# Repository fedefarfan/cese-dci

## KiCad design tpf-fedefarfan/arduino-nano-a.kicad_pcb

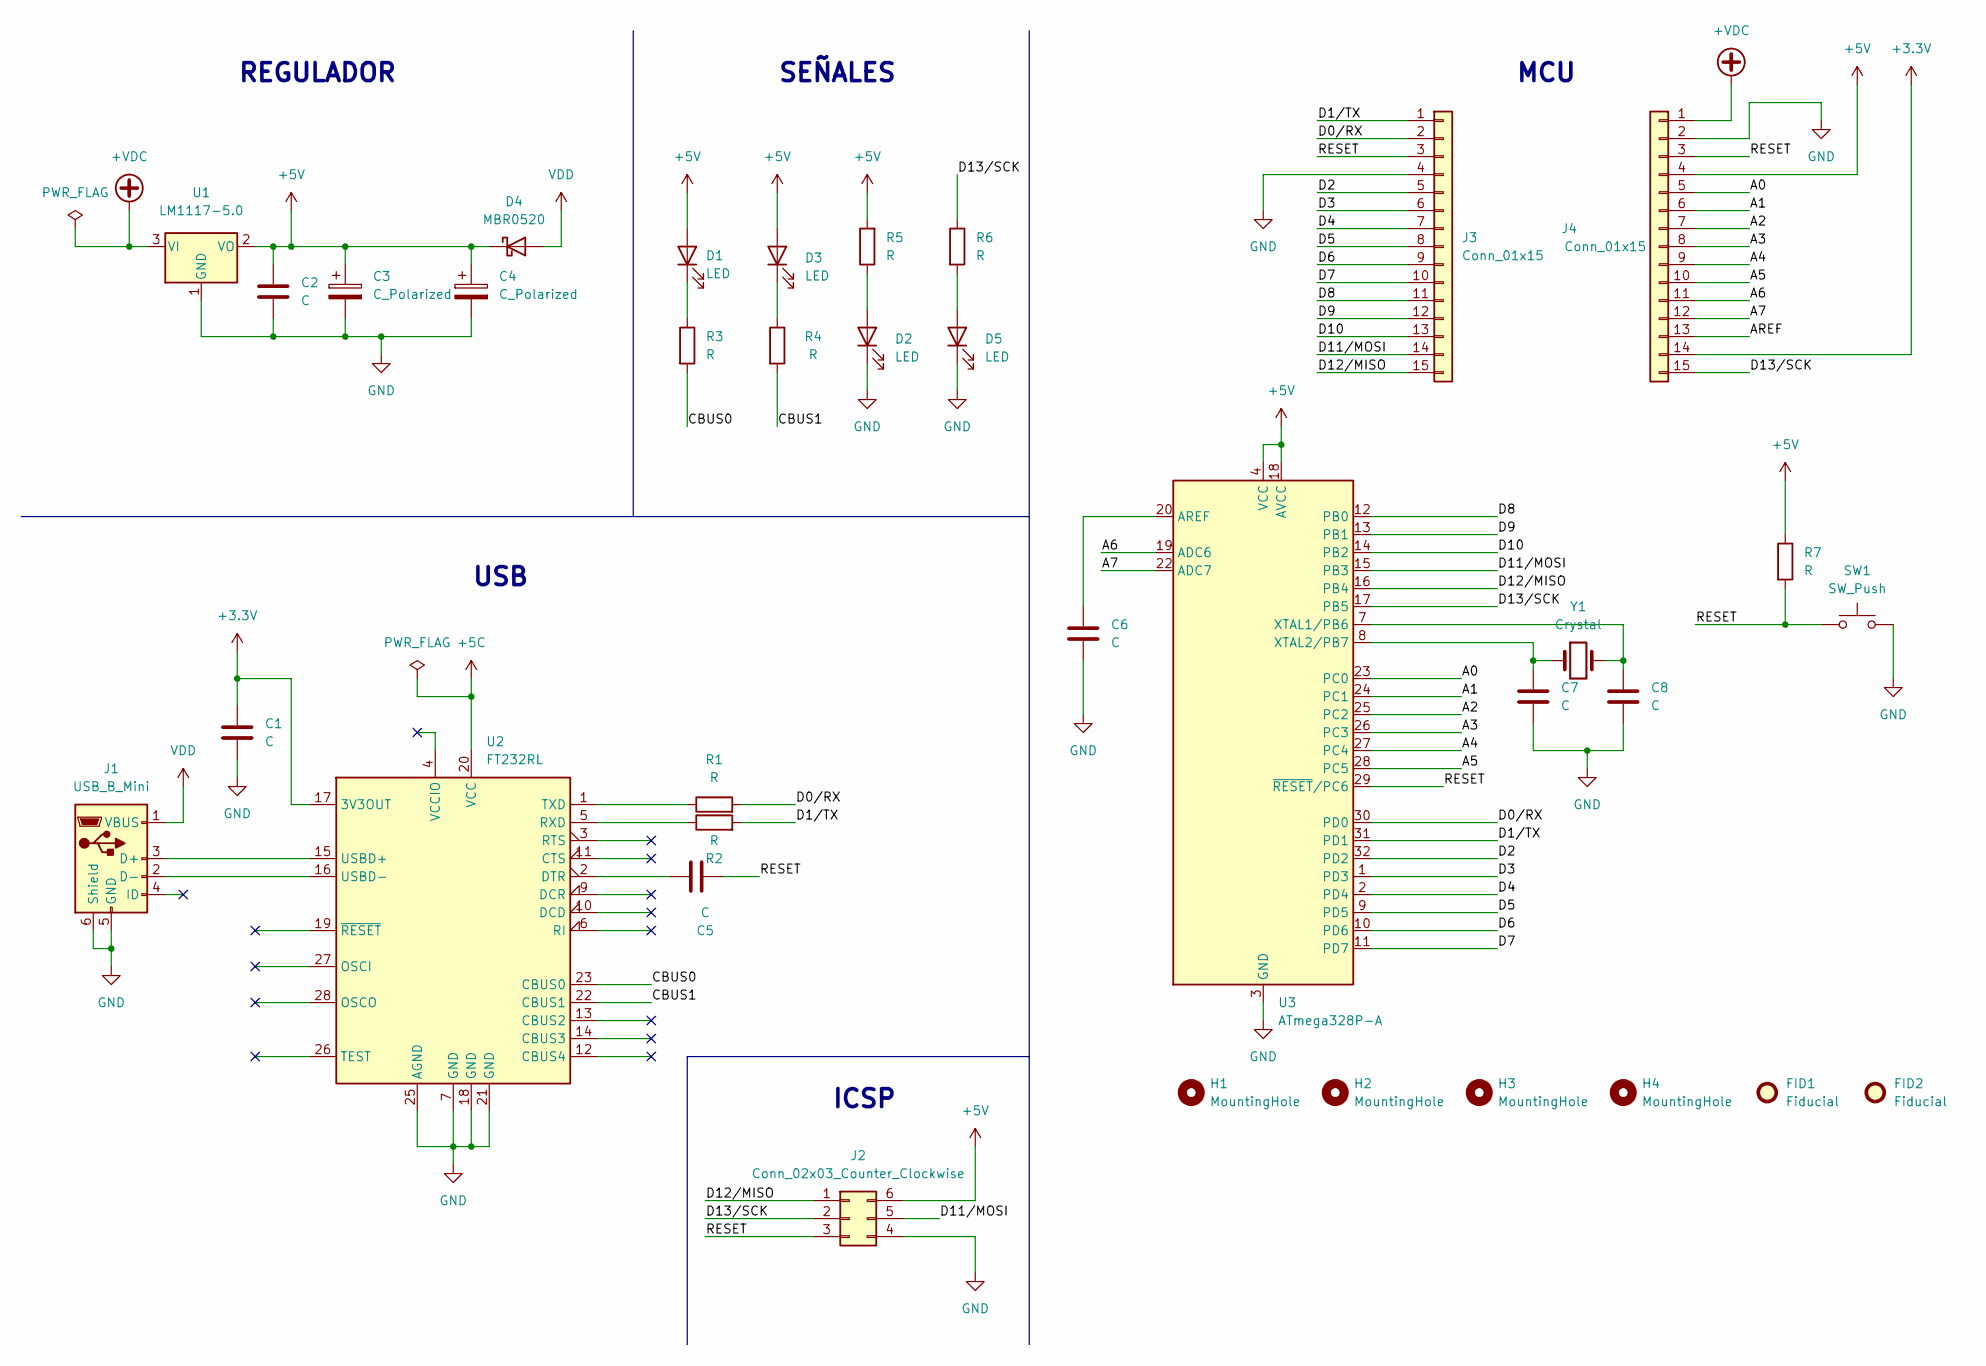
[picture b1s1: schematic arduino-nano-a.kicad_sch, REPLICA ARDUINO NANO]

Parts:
C1: C
C2, C5, C6, C7, C8: C; CP_EIA-3216-18_Kemet-A_Pad1.58x1.35mm_HandSolder
C3, C4: C_Polarized; CP_Elec_3x5.3
D1, D2, D3, D5: LED; LED_0805_2012Metric_Pad1.15x1.40mm_HandSolder
D4: MBR0520; D_SOD-123
FID1, FID2: Fiducial; Fiducial_1mm_Mask2mm
H1, H2, H3, H4: MountingHole; MountingHole_2.2mm_M2_ISO7380
J1: USB_B_Mini; USB_Mini-B_Lumberg_2486_01_Horizontal
J2: Conn_02x03_Counter_Clockwise; PinHeader_2x03_P2.54mm_Vertical
J3, J4: Conn_01x15; PinHeader_1x15_P2.54mm_Vertical
R1, R2, R3, R4, R5, R6, R7: R; R_0201_0603Metric
SW1: SW_Push; SW_SPST_FSMSM
U1: LM1117-5.0; SOT-223-3_TabPin2
U2: FT232RL; SSOP-28_5.3x10.2mm_P0.65mm
U3: ATmega328P-A; TQFP-32_7x7mm_P0.8mm
Y1: Crystal; Crystal_HC49-U_Vertical

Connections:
+3.3V: C1.1, J4.14, U2.17 (3V3OUT)
+5C: U2.20 (VCC)
+5V: C2.1, C3.1, C4.1, D1.2 (A), D3.2 (A), D4.1 (K), J2.6, J4.4, R5.2, R7.1, U1.2 (VO), U3.4 (VCC), U3.6 (VCC), U3.18 (AVCC)
+VDC: J4.1, U1.3 (VI)
/A0: J4.5, U3.23 (PC0)
/A1: J4.6, U3.24 (PC1)
/A2: J4.7, U3.25 (PC2)
/A3: J4.8, U3.26 (PC3)
/A4: J4.9, U3.27 (PC4)
/A5: J4.10, U3.28 (PC5)
/A6: J4.11, U3.19 (ADC6)
/A7: J4.12, U3.22 (ADC7)
/AREF: J4.13
/CBUS0: R3.2, U2.23 (CBUS0)
/CBUS1: R4.2, U2.22 (CBUS1)
/D0/RX: J3.2, R1.2, U3.30 (PD0)
/D1/TX: J3.1, R2.2, U3.31 (PD1)
/D2: J3.5, U3.32 (PD2)
/D3: J3.6, U3.1 (PD3)
/D4: J3.7, U3.2 (PD4)
/D5: J3.8, U3.9 (PD5)
/D6: J3.9, U3.10 (PD6)
/D7: J3.10, U3.11 (PD7)
/D8: J3.11, U3.12 (PB0)
/D9: J3.12, U3.13 (PB1)
/D10: J3.13, U3.14 (PB2)
/D11/MOSI: J2.5, J3.14, U3.15 (PB3)
/D12/MISO: J2.1, J3.15, U3.16 (PB4)
/D13/SCK: J2.2, J4.15, R6.1, U3.17 (PB5)
/RESET: C5.2, J2.3, J3.3, J4.2, J4.3, R7.2, SW1.1, U3.29 (~RESET/PC6)
GND: C1.2, C2.2, C3.2, C4.2, C6.2, C7.2, C8.2, D2.1 (K), D5.1 (K), J1.5 (GND), J1.6 (Shield), J2.4, J3.4, J4.2, SW1.2, U1.1 (GND), U2.7 (GND), U2.18 (GND), U2.21 (GND), U2.25 (AGND), U3.3 (GND), U3.5 (GND), U3.21 (GND)
unnamed: C5.1, U2.2 (DTR)
unnamed: C6.1, U3.20 (AREF)
unnamed: C7.1, U3.8 (XTAL2/PB7), Y1.1
unnamed: C8.1, U3.7 (XTAL1/PB6), Y1.2
unnamed: D1.1 (K), R3.1
unnamed: D2.2 (A), R5.1
unnamed: D3.1 (K), R4.1
unnamed: D5.2 (A), R6.2
unnamed: J1.2 (D-), U2.16 (USBD-)
unnamed: J1.3 (D+), U2.15 (USBD+)
unnamed: R1.1, U2.1 (TXD)
unnamed: R2.1, U2.5 (RXD)
VDD: D4.2 (A), J1.1 (VBUS)

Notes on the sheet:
USB
SEÑALES
MCU
REGULADOR
ICSP

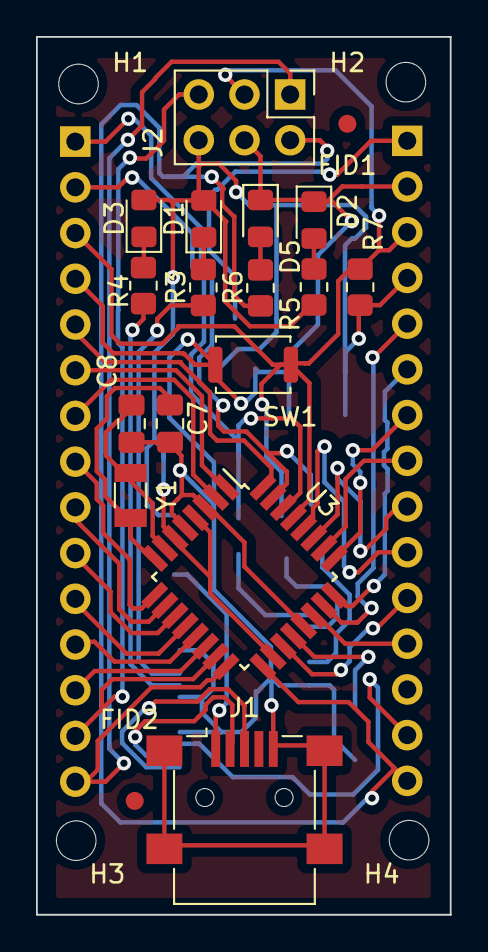
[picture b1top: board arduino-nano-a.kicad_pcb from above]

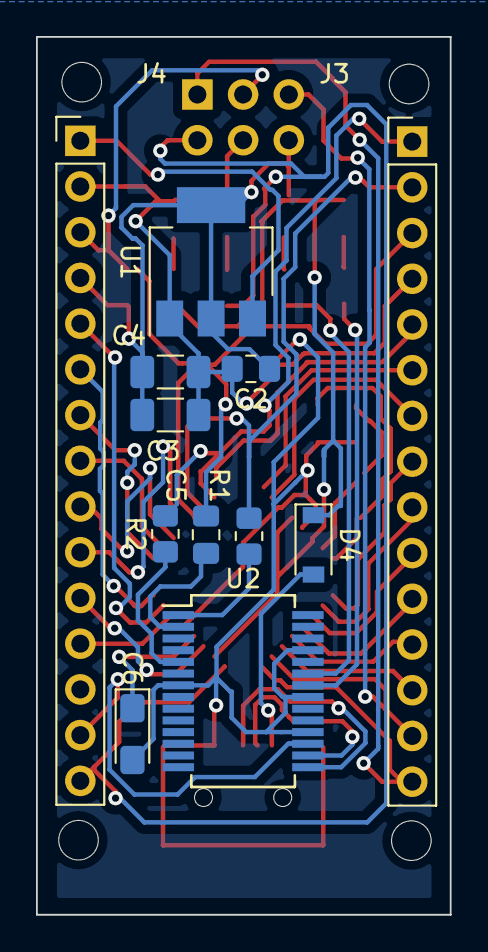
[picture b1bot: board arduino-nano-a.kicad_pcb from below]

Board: 2 copper layers, 23.0 x 48.8 mm, 34 parts (12 on the bottom side), 42 nets.

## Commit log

2022-07-28 Trabajo Final

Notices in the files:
tpf-fedefarfan/arduino-nano-a.kicad_pcb:
Licencia: CC BY-NC-SA
